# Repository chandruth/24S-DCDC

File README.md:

# 24S-DCDC — KiCad Project (skeleton pre-route)

**Status:** This is a *simplified, illustrative* routed board stub produced in-chat.  
It contains:
- A 100×100 mm outline with 4× M3 mounting holes (92 mm square pattern).
- XT90 input connector (J1) and three XT90 output connectors (J2=48V, J3=12V, J4=5V).
- Three "BuckBlock" placeholder footprints (B1 48V, B2 12V, B3 5V) with VIN/VOUT/GND pads.
- Thick copper tracks for VIN, GND, and each Vout to its XT90.
- **It is NOT a production layout**. You must replace placeholders with real footprints (LTC3895, FETs, inductors, caps), re-route with correct widths/clearances, and then generate Gerbers.

## Nets
- VIN, GND
- V48, V12, V5

## How to use
1. Open `hardware/kicad/24S-DCDC.kicad_pcb` in KiCad 7/8.
2. Replace placeholder footprints with real ones and import schematics/netlist.
3. Re-route power and high-speed loops, add planes/zones, clearances, and DRC rules.
4. Plot Gerbers/Drills via KiCad's `kicad-cli` or GUI.

> This file only serves as a *bridge* to get you unblocked while I prepare the full production layout offline.

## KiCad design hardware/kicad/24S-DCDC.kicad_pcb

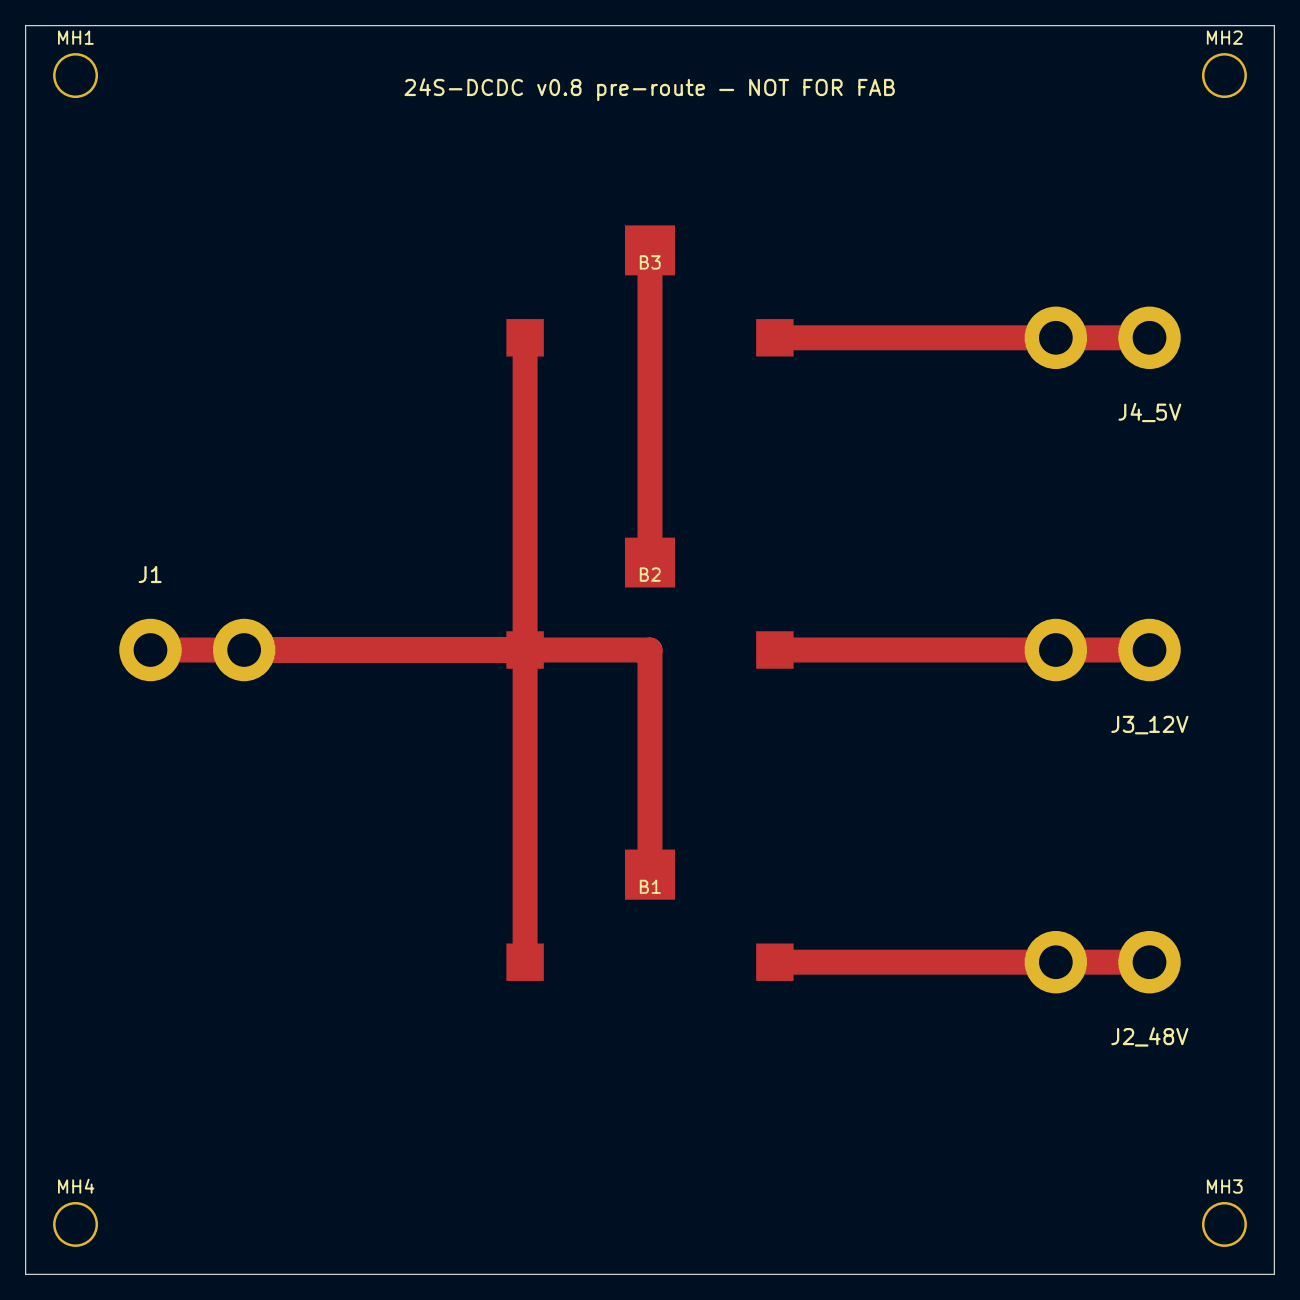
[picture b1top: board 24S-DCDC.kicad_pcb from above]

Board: 2 copper layers, 100.0 x 100.0 mm, 11 parts (0 on the bottom side), 5 nets.

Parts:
B1: 48V_Buck; BuckBlock
B2: 12V_Buck (Master); BuckBlock
B3: 5V_Buck; BuckBlock
J1: J1; XT90_Simplified
J2_48V: J2_48V; XT90_Simplified
J3_12V: J3_12V; XT90_Simplified
J4_5V: J4_5V; XT90_Simplified
MH1, MH2, MH3, MH4: M3

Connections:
GND: B1.3, B2.3, B3.3, J1.2, J2_48V.2, J3_12V.2, J4_5V.2
V5: B3.2, J4_5V.1
V12: B2.2, J3_12V.1
V48: B1.2, J2_48V.1
VIN: B1.1, B2.1, B3.1, J1.1
